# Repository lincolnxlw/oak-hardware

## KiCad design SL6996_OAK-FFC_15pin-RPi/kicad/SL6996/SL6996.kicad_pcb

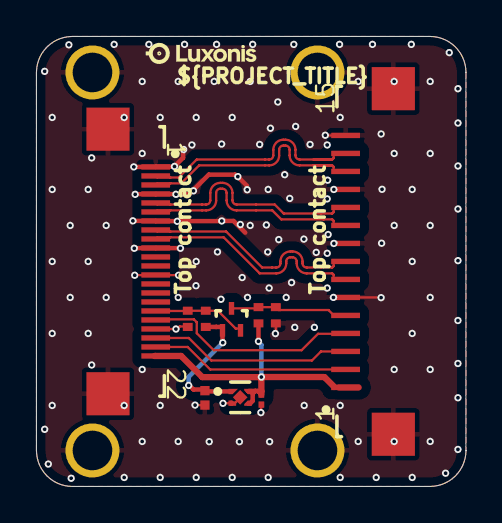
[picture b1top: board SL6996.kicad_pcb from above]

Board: 4 copper layers, 23.9 x 25.0 mm, 10 parts (0 on the bottom side), 14 nets.

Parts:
C1: GRM155R60J106ME15D; CAPC0402(1005)70_L
C2: GRM033R61A105ME15D; CAPC0201(0603)33_L
J1: F32Q-1A7H1-11022
J2: F52Q-1A7H1-11015; F52Q-1A7H1-11015-Footprint-1
Q1: RE1C002UNTCL
R1, R2, R3, R4: RC0402FR-1310KL; RESC0402(1005)_L
U1: NCP114AMX180TBG; FP-517CU-MFG

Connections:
1V8: C1.2, Q1.1, R1.2, U1.1
3V3: C2.2, J1.22, J2.1, R2.2, U1.3, U1.4
ENABLE: J1.17, Q1.2, R1.1, R3.2
ENABLE_RPI: J2.5, Q1.3, R2.1, R4.2
GND: C1.1, C2.1, J1.1, J1.4, J1.7, J1.10, J1.13, J1.19, J1.MP1, J1.MP2, J2.6, J2.9, J2.12, J2.15, J2.MP1, J2.MP2, R3.1, R4.1, U1.2, U1.5
GPI: J1.18, J2.4
I2C_SCL_RPI: J1.20, J2.3
I2C_SDA_RPI: J1.21, J2.2
MIPI_C_N: J1.8, J2.8
MIPI_C_P: J1.9, J2.7
MIPI_D0_N: J1.2, J2.14
MIPI_D0_P: J1.3, J2.13
MIPI_D1_N: J1.5, J2.11
MIPI_D1_P: J1.6, J2.10

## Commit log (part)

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2026-04-13 Update part number for FFC26P
2026-04-13 Update kicad production files
